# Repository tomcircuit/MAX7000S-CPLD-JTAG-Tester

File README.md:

# MAX7000S CPLD JTAG Tester

This set of design files pertains to a testboard for EPM7128SLx84 CPLDs

I am a big fan of the EPM7128SLC84 CPLD device. It supports 5V I/O for retroputing projects,
has enough macrocells to support medium complexity projects (e.g. glue for hd6309 SBC), etc.
This device is EOL from Altera (Intel) but can be found on the 'gray-market' (e.g. eBay).
However, many of the devices found from such sellers are not usable because the JTAG pins
have been re-assigned to I/O. Once this is done, the CPLD can only be reset to factory
default state with hard-to-find Altera parallel programming equipment. 

So, this project was born to allow CPLD devices to be temporarily connected to an Altera USB 
blaster (or compatible) to see if the JTAG is operational. A 3M PLCC socket is used for this
project, which might be a bit hard to find, but is well worth the effort.

More up-to-date information on the SBC can be found on the Hackaday project page:
####

This work is licensed under the Creative Commons Attribution-ShareAlike 4.0 International License. 
To view a copy of this license, visit http://creativecommons.org/licenses/by-sa/4.0/.

Tom LeMense
2/6/2020

tomcircuit@gmail.com
@TomLeMense

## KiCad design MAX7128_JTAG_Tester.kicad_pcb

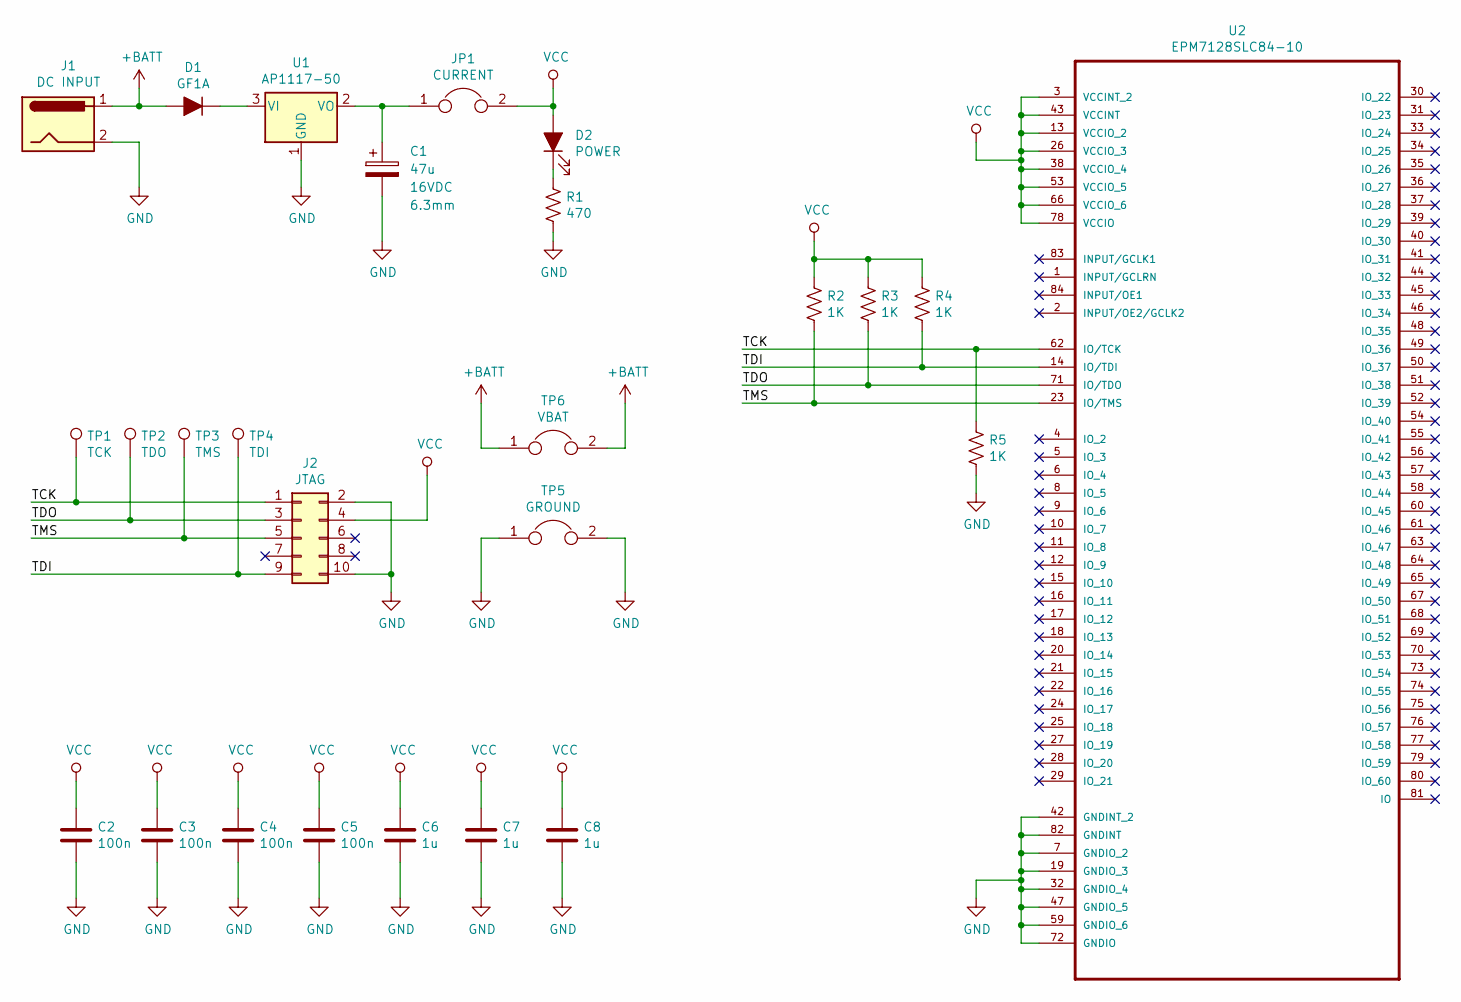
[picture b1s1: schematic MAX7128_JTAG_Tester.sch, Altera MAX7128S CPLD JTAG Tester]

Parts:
C1: 47u; CP_Elec_6.3x4.5; Voltage 16VDC
C2, C3, C4, C5: 100n; C_0603_HandSoldering
C6, C7, C8: 1u; C_0603_HandSoldering
D1: GF1A; D_SMA_Handsoldering
D2: POWER; LED_0805_HandSoldering
J1: DC INPUT; Barrel_Jack_CUI_PJ-102AH
J2: JTAG; SDL-110-X-XX_2x05
JP1: CURRENT; Pin_Header_Straight_1x02_Pitch2.54mm
R1: 470; R_0805_HandSoldering
R2, R3, R4, R5: 1K; R_0805_HandSoldering
TP1: TCK; Measurement_Point_Square-SMD-Pad_Big
TP2: TDO; Measurement_Point_Square-SMD-Pad_Big
TP3: TMS; Measurement_Point_Square-SMD-Pad_Big
TP4: TDI; Measurement_Point_Square-SMD-Pad_Big
TP5: GROUND; Pin_Header_Straight_1x02_Pitch2.54mm
TP6: VBAT; Pin_Header_Straight_1x02_Pitch2.54mm
U1: AP1117-50; SOT-223-3_TabPin2
U2: EPM7128SLC84-10; 284-5756-00-1102

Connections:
+BATT: D1.2 (A), J1.1, TP6.1, TP6.2
/TCK: J2.1, R5.1, TP1.1, U2.62 (IO/TCK)
/TDI: J2.9, R4.2, TP4.1, U2.14 (IO/TDI)
/TDO: J2.3, R3.2, TP2.1, U2.71 (IO/TDO)
/TMS: J2.5, R2.2, TP3.1, U2.23 (IO/TMS)
GND: C1.2, C2.2, C3.2, C4.2, C5.2, C6.2, C7.2, C8.2, J1.2, J2.2, J2.10, R1.2, R5.2, TP5.1, TP5.2, U1.1 (GND), U2.7 (GNDIO_2), U2.19 (GNDIO_3), U2.32 (GNDIO_4), U2.42 (GNDINT_2), U2.47 (GNDIO_5), U2.59 (GNDIO_6), U2.72 (GNDIO), U2.82 (GNDINT)
unnamed: C1.1, JP1.1, U1.2 (VO)
unnamed: D1.1 (K), U1.3 (VI)
unnamed: D2.1 (K), R1.1
VCC: C2.1, C3.1, C4.1, C5.1, C6.1, C7.1, C8.1, D2.2 (A), J2.4, JP1.2, R2.1, R3.1, R4.1, U2.3 (VCCINT_2), U2.13 (VCCIO_2), U2.26 (VCCIO_3), U2.38 (VCCIO_4), U2.43 (VCCINT), U2.53 (VCCIO_5), U2.66 (VCCIO_6), U2.78 (VCCIO)

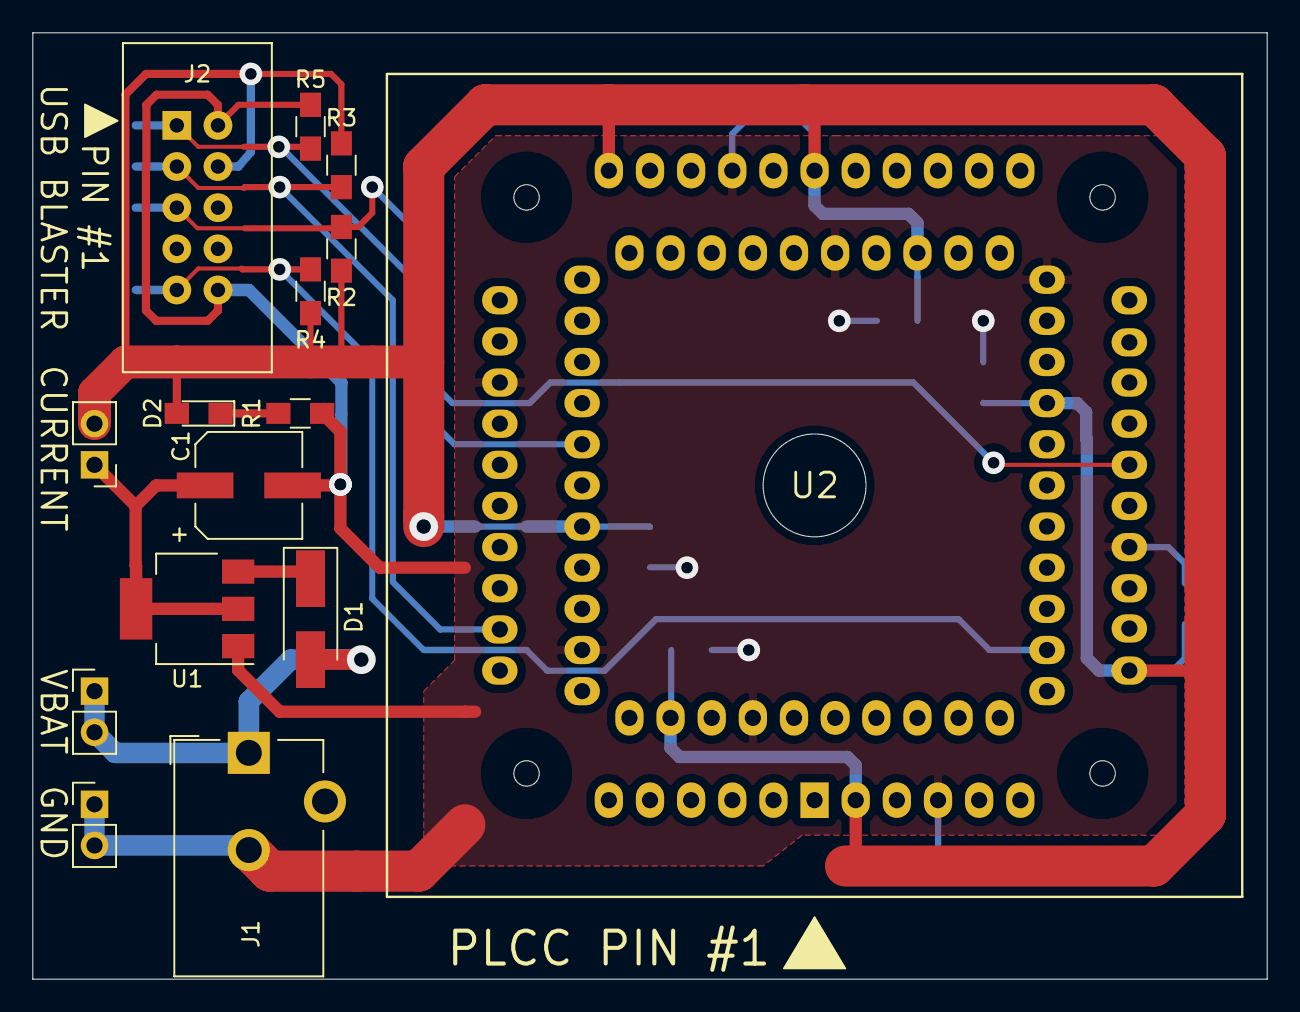
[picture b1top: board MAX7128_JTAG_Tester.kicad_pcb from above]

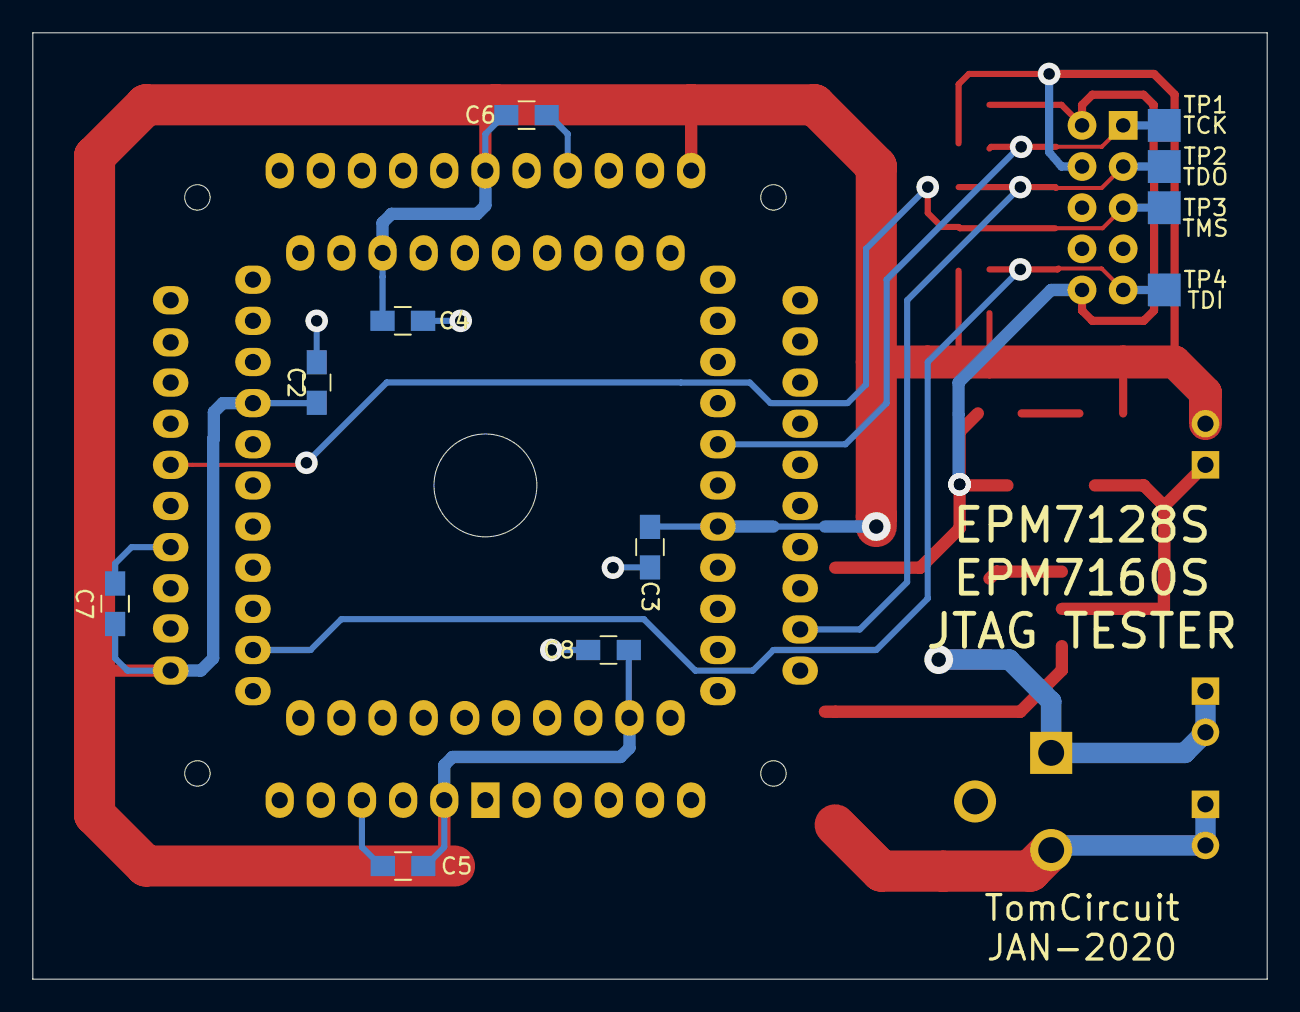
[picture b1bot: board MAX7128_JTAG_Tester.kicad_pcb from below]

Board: 2 copper layers, 76.2 x 58.4 mm, 26 parts (11 on the bottom side), 10 nets.

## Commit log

2020-02-06 Initial checking
    PCB fabbed, build, and tested.
2020-02-06 Confirmed push to Github
2020-02-06 Added assembled board photos
